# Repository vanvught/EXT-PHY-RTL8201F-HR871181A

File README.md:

# External PHY RTL8201F with HR871181A

More information [https://www.gd32-dmx.org/ethernet.html](https://www.gd32-dmx.org/ethernet.html)

New KiCad -> [https://github.com/vanvught/KiCad-EXT-PHY-RTL8201F](https://github.com/vanvught/KiCad-EXT-PHY-RTL8201F)

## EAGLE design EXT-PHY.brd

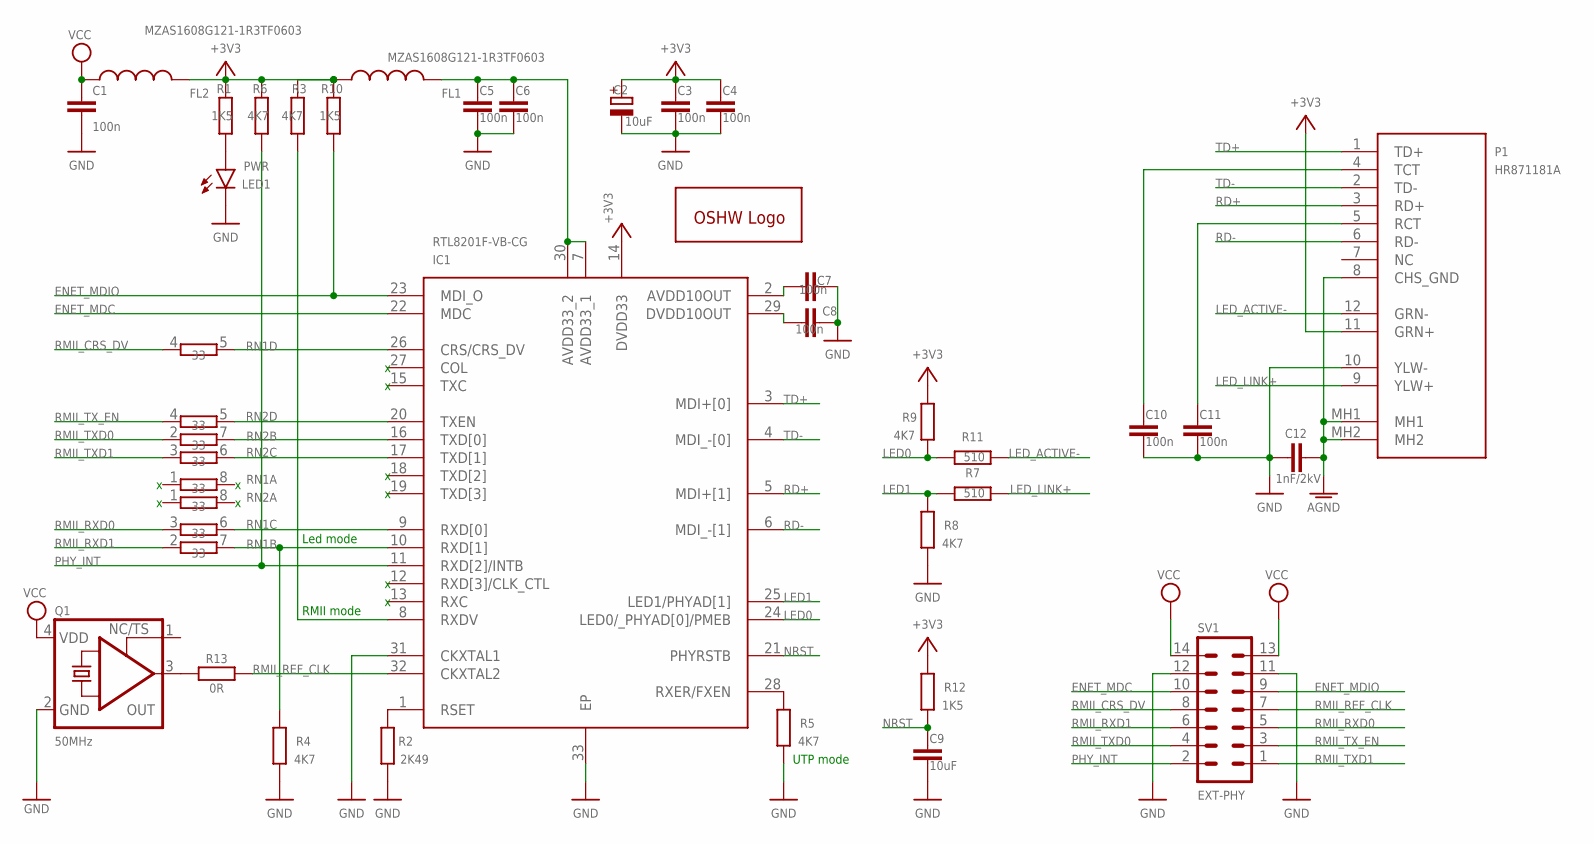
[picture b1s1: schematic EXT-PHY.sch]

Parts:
C1, C3, C4, C5, C6, C7, C8, C10, C11: 100n; C0603; JLCPCB C14663
C2: 10uF; A/3216-18R; JLCPCB C7171
C9: 10uF; C0603; JLCPCB C19702
C12: 1nF/2kV; C1206; JLCPCB C9196
FL1, FL2: MZAS1608G121-1R3TF0603; 0603
GOLD_ORB_SM1: OSHWLOGOLOGO5MM; OSHW_5MM
IC1: RTL8201F-VB-CG; QFN50P500X500X100-33N
LED1: PWR; CHIP-LED0603; JLCPCB C72043
P1: HR871181A
Q1: 50MHz; 3.2X2.5_KXO-V96; JLCPCB C160451
R1, R10, R12: 1K5; R0603; JLCPCB C22843
R2: 2K49; R0603; JLCPCB C100897
R3, R4, R5, R6, R8, R9: 4K7; R0603; JLCPCB C23162
R7, R11: 510; R0603; JLCPCB C23193
R13: 0R; R0603; JLCPCB C115304
RN1, RN2: 33; 4X0402ARV341; JLCPCB C25501
SV1: EXT-PHY; MA07-2W

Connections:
50MHZ: Q1.3 (OUT), R13.1
+3V3: C2.+, C3.1, C4.1, FL1.1, FL2.2, IC1.14 (DVDD33), P1.11 (GRN+), R1.2, R3.1, R6.2, R9.2, R10.2, R12.2
AGND: C12.2, P1.8 (CHS_GND), P1.MH1, P1.MH2
AVDD: C5.1, C6.1, FL1.2, IC1.7 (AVDD33_1), IC1.30 (AVDD33_2)
ENET_MDC: IC1.22 (MDC), SV1.10
ENET_MDIO: IC1.23 (MDI_O), R10.1, SV1.9
GND: C1.2, C2.-, C3.2, C4.2, C5.2, C6.2, C7.2, C8.1, C9.2, C10.2, C11.2, C12.1, IC1.31 (CKXTAL1), IC1.33 (EP), LED1.C, P1.10 (YLW-), Q1.2 (GND), R2.2, R4.1, R5.1, R8.1, SV1.11, SV1.12
LED0: IC1.24 (LED0/_PHYAD[0]/PMEB), R9.1, R11.2
LED1: IC1.25 (LED1/PHYAD[1]), R7.2, R8.2
LED_ACTIVE-: P1.12 (GRN-), R11.1
LED_LINK+: P1.9 (YLW+), R7.1
unnamed: LED1.A, R1.1
unnamed: IC1.1 (RSET), R2.1
unnamed: IC1.8 (RXDV), R3.2
unnamed: C8.2, IC1.29 (DVDD10OUT)
unnamed: IC1.28 (RXER/FXEN), R5.2
unnamed: C11.1, P1.5 (RCT)
unnamed: C10.1, P1.4 (TCT)
unnamed: C7.1, IC1.2 (AVDD10OUT)
NRST: C9.1, IC1.21 (PHYRSTB), R12.1
PHY_INT: IC1.11 (RXD[2]/INTB), R6.1, SV1.2
RD+: IC1.5 (MDI+[1]), P1.3 (RD+)
RD-: IC1.6 (MDI_-[1]), P1.6 (RD-)
RMII_CRS_DV: RN1.4 (1), SV1.8
RMII_REF_CLK: IC1.32 (CKXTAL2), R13.2, SV1.7
RMII_RXD0: RN1.3 (1), SV1.5
RMII_RXD1: RN1.2 (1), SV1.6
RMII_TXD0: RN2.2 (1), SV1.4
RMII_TXD1: RN2.3 (1), SV1.1
RMII_TX_EN: RN2.4 (1), SV1.3
RXD0: IC1.9 (RXD[0]), RN1.6 (2)
RXD1: IC1.10 (RXD[1]), R4.2, RN1.7 (2)
RXDV: IC1.26 (CRS/CRS_DV), RN1.5 (2)
TD+: IC1.3 (MDI+[0]), P1.1 (TD+)
TD-: IC1.4 (MDI_-[0]), P1.2 (TD-)
TXD0: IC1.16 (TXD[0]), RN2.7 (2)
TXD1: IC1.17 (TXD[1]), RN2.6 (2)
TXEN: IC1.20 (TXEN), RN2.5 (2)
VCC: C1.1, FL2.1, Q1.4 (VDD), SV1.13, SV1.14

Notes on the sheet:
RMII mode
UTP mode
Led mode

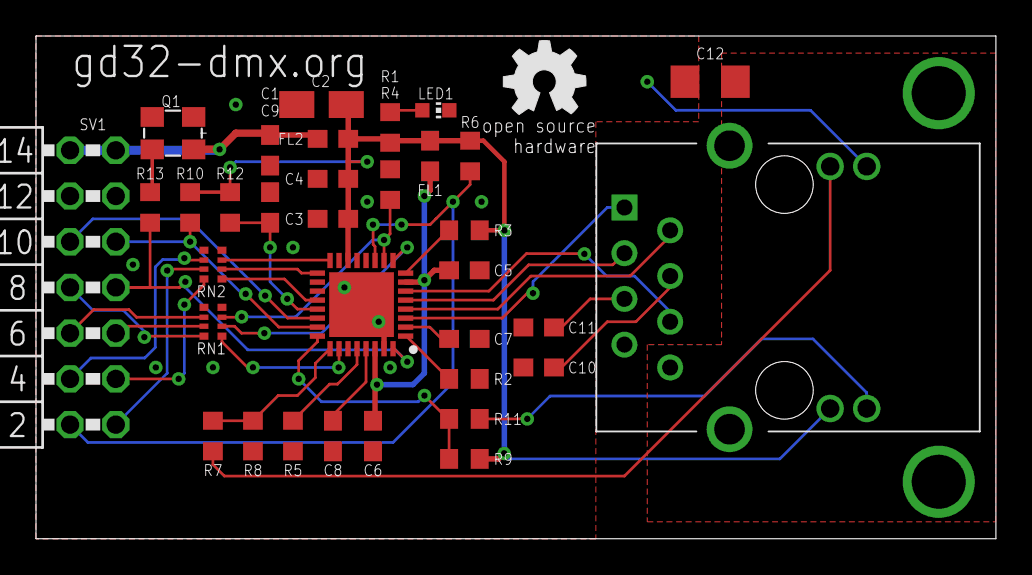
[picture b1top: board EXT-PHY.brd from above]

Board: 2 copper layers, 53.3 x 27.9 mm, 35 parts (0 on the bottom side), 39 nets.

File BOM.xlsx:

Qty | Designator | Footprint | Comment | LCSC Part #
9 | C1, C3, C4, C5, C6, C7, C8, C10, C11 | C0603 | 100n | C14663
1 | C12 | C1206 | 1nF/2kV | C9196
1 | C2 | A/3216-18R | 10uF | C7171
1 | C9 | C0603 | 10uF | C19702
2 | FL1, FL2 | 603 | MZAS1608G121-1R3TF | C709642
1 | IC1 | QFN50P500X500X100-33N | RTL8201F-VB-CG | C45044
1 | LED1 | CHIP-LED0603 | PWR | C72043
1 | P1 | HR871181A | HR871181A | C49312
1 | Q1 | 3.2X2.5_KXO-V96 | 50MHz | C160451
3 | R1, R10, R12 | R0603 | 1K5 | C22843
1 | R2 | R0603 | 2K49 | C100897
6 | R3, R4, R5, R6, R8, R9 | R0603 | 4K7 | C23162
2 | R7, R11 | R0603 | 510 | C23193
1 | R13 | R0603 | 0 | C115304
2 | RN1, RN2 | 4X0402ARV341 | 33 | C25501
33

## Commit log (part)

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2024-03-03 Initial commit
    @particlerain

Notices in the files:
parts and their libraries:
crystal-geyer_V1_0: Copyright: Geyer-Electronic
